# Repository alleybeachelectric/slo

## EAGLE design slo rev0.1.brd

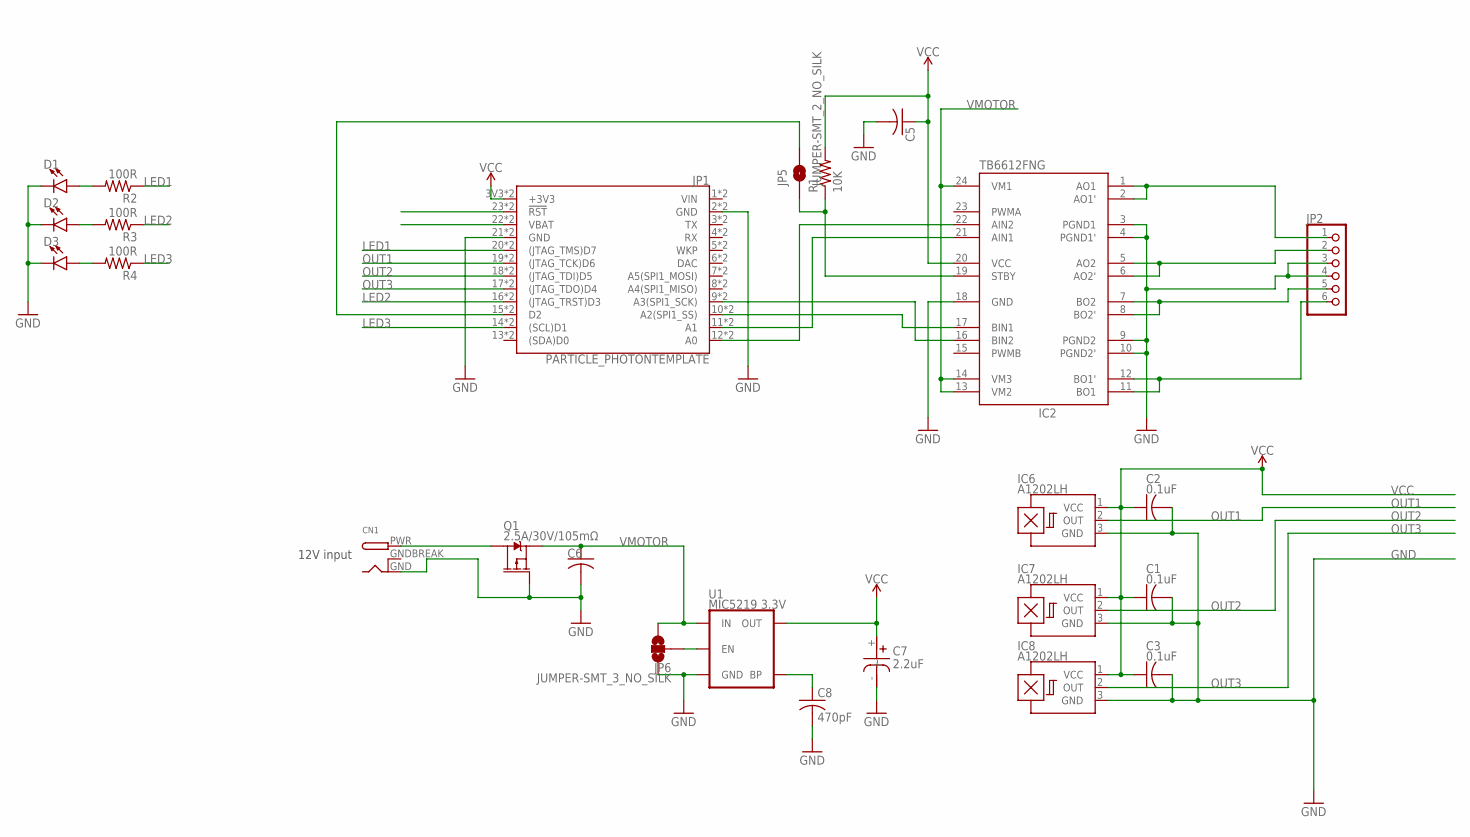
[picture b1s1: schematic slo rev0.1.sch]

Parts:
C1, C2, C3: 0.1uF; C0603
C5, C6: C-USC1206; C1206
C7: 2.2uF; 0603_TANTALUM_CAPACITOR
C8: 470pF; C0603
CN1: DCBARRELPTH; DCJACK_2MM_PTH
D1, D2, D3: LED-FKIT-1206; FKIT-LED-1206
IC2: TB6612FNG; SSOP24
IC6, IC7, IC8: A1202LH; SOT23-W
JP1: PARTICLE_PHOTONTEMPLATE; PARTICLE_PHOTON_TEMPLATE
JP2: PINHD-1X6-3.5MM; 1X06-3.5MM
JP5: JUMPER-SMT_2_NO_SILK; SMT-JUMPER_2_NO_SILK
JP6: JUMPER-SMT_3_NO_SILK; SMT-JUMPER_3_NO_SILK
Q1: 2.5A/30V/105mΩ; SOT23-3
R1: 10K; R1206
R2, R3, R4: 100R; R1206
U1: MIC5219 3.3V; SOT23-5

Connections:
GND: C1.2, C2.2, C3.2, C5.2, C6.2, C7.-, C8.2, CN1.GND, D1.C, D2.C, D3.C, IC2.3 (PGND1), IC2.4 (PGND1'), IC2.9 (PGND2), IC2.10 (PGND2'), IC2.18 (GND), IC6.3 (GND), IC7.3 (GND), IC8.3 (GND), JP1.2 (GND), JP1.21 (GND), JP1.GND@0 (GND), JP1.GND@2 (GND), JP2.3, JP2.4, JP6.1, Q1.1 (G), U1.2 (GND)
GNDBREAK: CN1.GNDBREAK
LED1: JP1.20 ((JTAG_TMS)D7), JP1.D7 ((JTAG_TMS)D7), R2.1
LED2: JP1.16 ((JTAG_TRST)D3), JP1.D3 ((JTAG_TRST)D3), R3.1
LED3: JP1.14 ((SCL)D1), JP1.D1 ((SCL)D1), R4.1
unnamed: IC2.1 (AO1), IC2.2 (AO1'), JP2.1
unnamed: IC2.5 (AO2), IC2.6 (AO2'), JP2.2
unnamed: IC2.7 (BO2), IC2.8 (BO2'), JP2.5
unnamed: IC2.11 (BO1), IC2.12 (BO1'), JP2.6
unnamed: CN1.PWR, Q1.3 (D)
unnamed: IC2.19 (STBY), JP5.1, R1.1
unnamed: D1.A, R2.2
unnamed: JP1.22 (VBAT), JP1.VBAT
unnamed: JP6.2, U1.3 (EN)
unnamed: JP1.23 (!RST!), JP1.RST (!RST!)
unnamed: IC2.22 (AIN2), JP1.12 (A0), JP1.A0
unnamed: IC2.21 (AIN1), JP1.11 (A1), JP1.A1
unnamed: IC2.17 (BIN1), JP1.10 (A2(SPI1_SS)), JP1.A2 (A2(SPI1_SS))
unnamed: IC2.16 (BIN2), JP1.9 (A3(SPI1_SCK)), JP1.A3 (A3(SPI1_SCK))
unnamed: JP1.15 (D2), JP1.D2, JP5.2
unnamed: D2.A, R3.2
unnamed: C8.1, U1.4 (BP)
unnamed: D3.A, R4.2
OUT1: IC6.2 (OUT), JP1.19 ((JTAG_TCK)D6), JP1.D6 ((JTAG_TCK)D6)
OUT2: IC7.2 (OUT), JP1.18 ((JTAG_TDI)D5), JP1.D5 ((JTAG_TDI)D5)
OUT3: IC8.2 (OUT), JP1.17 ((JTAG_TDO)D4), JP1.D4 ((JTAG_TDO)D4)
VCC: C1.1, C2.1, C3.1, C5.1, C7.+, IC2.20 (VCC), IC6.1 (VCC), IC7.1 (VCC), IC8.1 (VCC), JP1.3V3 (+3V3), JP1.24 (+3V3), R1.2, U1.5 (OUT)
VIN: JP1.1 (VIN), JP1.VIN
VMOTOR: C6.1, IC2.13 (VM2), IC2.14 (VM3), IC2.24 (VM1), JP6.3, Q1.2 (S), U1.1 (IN)

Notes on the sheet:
12V input

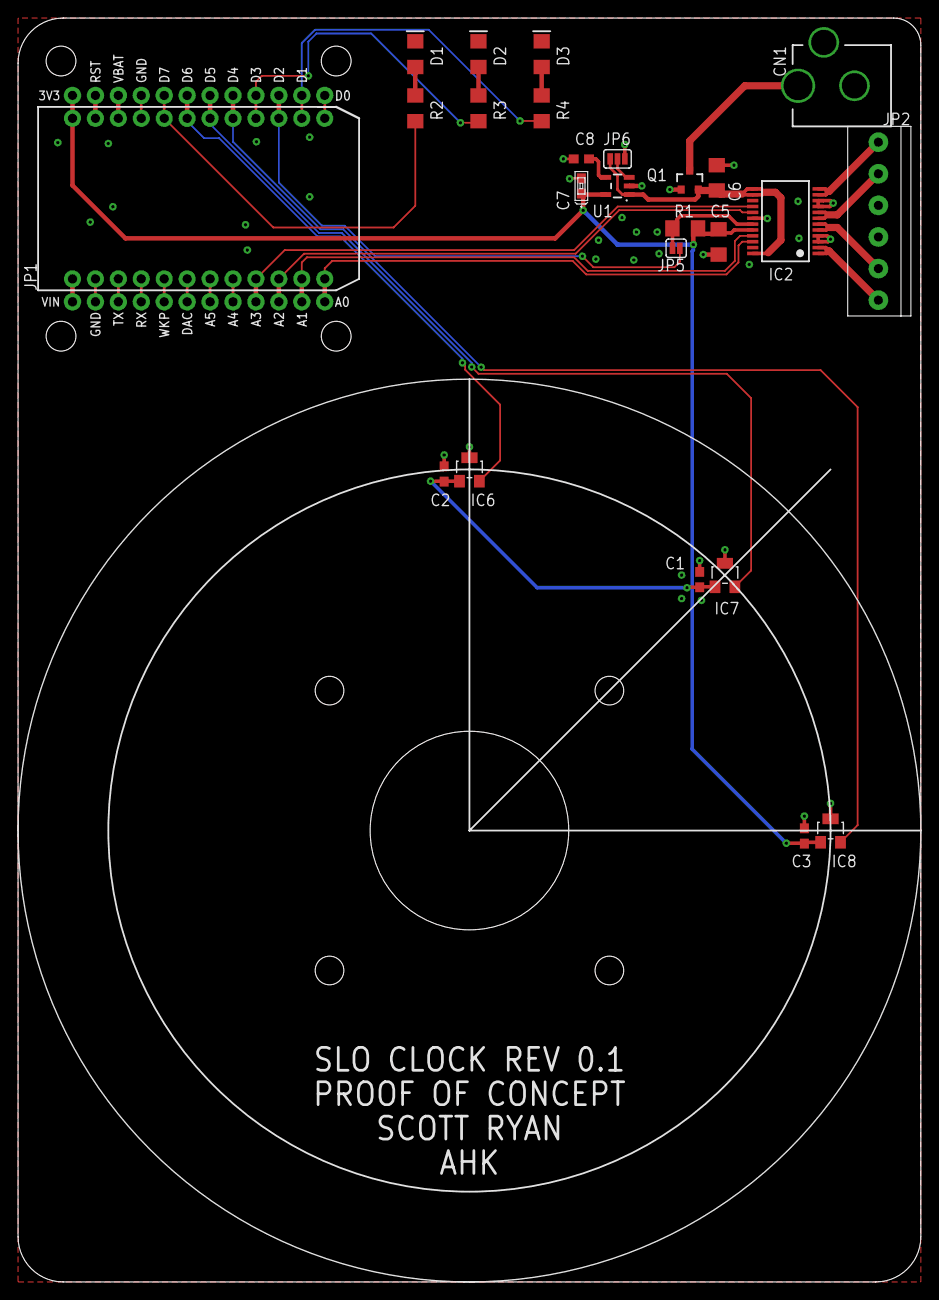
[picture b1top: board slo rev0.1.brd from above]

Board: 2 copper layers, 100.0 x 140.0 mm, 25 parts (0 on the bottom side), 28 nets.

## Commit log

2018-07-10 initial commit
    the pieces are kinda there
2018-07-11 added to circuit
2018-07-17 added more goodies
2018-07-19 removed a hall sensor
    need to create option to house an encoder

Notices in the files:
parts and their libraries:
SparkFun-Boards: Licensing: Creative Commons ShareAlike 4.0 International - https://creativecommons.org/licenses/by-sa/4.0
